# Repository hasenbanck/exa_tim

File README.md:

# EXA_tim

EXA_tim is a wristwatch that uses GNSS for time synchronization.

# Features

- 32bit STM32L0 MCU
- GNSS time synchronization (UTC)
- 1.54 inch e-paper display
- 4 buttons
- CR2032 battery

Currently we are aiming for 2-3 months of operation with one battery.

# Case

The case is designed in Fusion 360 and can be viewed here:
https://a360.co/2LLzCpt

A current snapshot is included in the source repository.

The case is designed to be 3D printable and uses a NATO strap.

If you want to 3D print them, you need to either use Fusion 360 or
FreeCAD to export the three components as STL files.

I printed them in PLA and PETG with good results. Low warp material
hightly recommended, since dimensional accuracy is key.

I designed the parts for a printer that can handle 0.1 mm clearance.
If you need looser clearance, please change the Fusion 360 user
variable "Clearance" for your needed value.

# Firmware

The firmware uses the STM32 HAL. It can be build by either using cmake
with the ARM GCC toolchain or by using Atollic TrueStudio.

For the CMAKE build, you need to provide the ARM GCC toolchain in the
PATH of your system. You can choose any CMAKE target that you like
to use. I personaly use ninja.

```bash
cd firmware
cmake -DCMAKE_TOOLCHAIN_FILE=arm-gcc-toolchain.cmake -G Ninja .
ninja
```

You can change add a ```-DCMAKE_BUILD_TYPE=Debug``` to the CMAKE
command to produce a debug build.

# Flashing

To programm the watch we are using the 10 pin 1.27mm (0.05") Cortex Debug
header. You need a programmer that can programm an ARM using the SWD
protocol.

A ST-Link V2 (and it's clones), a JLink (mini) or a blackmagic programmer
should work fine.

We included a OpenOCD file as an example how to programm the firmware.

You can also use any available flashing software available. For example:
 - OpenOCD
 - STM32CubeProgrammer
 - STM32 ST-Link utility
 - Segger J-Link JFlash (lite)

# License

The hardware components (case and PCB) are licensed under the CERN Open
Hardware Licence v1.2

The software components (firmware) are licensed under GPLv3.

The pcb/packages3d files are excluded from these license.

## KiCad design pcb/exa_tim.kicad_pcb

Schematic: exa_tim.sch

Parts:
BT1: 3034TR; BatteryHolder_Keystone_3034_1x20mm
C1, C6, C12, C13: 4.7uF; C_0603_1608Metric
C2, C3: 4pF; C_0603_1608Metric
C4, C5, C7, C9, C10, C11, C14, C17: 100nF; C_0603_1608Metric
C8, C15, C16, C18, C19, C20, C21, C22, C23, C24: 1uF; C_0603_1608Metric
D1, D2, D3, D4, D5, D6, D7: MBR0530; D_SOD-123
J1: 20021112-00010T4LF; PinHeader_2x05_P1.27mm_Horizontal
J2: FH12-24S-0.5SH(55); Hirose_FH12-24S-0.5SH_1x24-1MP_P0.50mm_Horizontal
L1: LPS4018-683MRB; L_Coilcraft_LPS4018
LS1: CUI_CSS-0575A-SMT
Q1, Q2: SI2333DS-T1-E3; SOT-23
Q3: DMN3067LW-7; SOT-323_SC-70
R1, R2, R5, R6: 1M; R_0603_1608Metric
R3, R4: 220; R_0603_1608Metric
R7: 3; R_0603_1608Metric
SW1, SW2, SW3, SW4: TL3305CF260QG; TL3305
U1: STM32L071KZUx; QFN-32-1EP_5x5mm_P0.5mm_EP3.45x3.45mm
U2: CAM-M8C-0; LCC100P960X1400X210-31N
Y1: ST2012SB32768B0HPWBB; Crystal_SMD_TXC_9HT11-2Pin_2.0x1.2mm_HandSoldering

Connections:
3V: BT1.1, C1.2, C4.2, C6.2, C7.2, C8.2, C9.2, C10.2, C13.1, J1.1, L1.1, Q1.2, Q2.2, R2.2, R5.2, SW1.1, SW2.1, SW3.1, SW4.1, U1.5 (VDDA), U1.17 (VDD), U1.24 (VDDIO2), U1.32 (VDD)
/ALARM: LS1.1, U1.7 (PA1)
/BTN1: D1.2, SW1.2, U1.27 (PB5)
/BTN2: D2.2, SW2.2, U1.26 (PB4)
/BTN3: D3.2, SW3.2, U1.29 (PB7)
/BTN4: D4.2, SW4.2, U1.28 (PB6)
/BUSY: J2.9, U1.12 (PA6)
/CS: J2.12, U1.18 (PA8)
/DC: J2.11, U1.14 (PB0)
/DISP_EN: Q2.1, R5.1, U1.10 (PA4)
/GDR: J2.2, Q3.1, R6.1
/GNSS_EN: Q1.1, R2.1, U1.22 (PA12)
/MOSI: J2.14, U1.13 (PA7)
/NRST: C5.2, J1.10, U1.3 (NRST)
/PREVGH: C21.1, D7.1, J2.21
/PREVGL: C23.1, D6.2, J2.23
/RESE: J2.3, Q3.2, R7.1
/RESET: J2.10, U1.15 (PB1)
/RF: U2.16, U2.17
/RX: R3.2, U1.9 (PA3)
/RX_GNSS: R4.1, U2.26
/SCK: J2.13, U1.11 (PA5)
/SWCLK: J1.4, U1.25 (PA14)
/SWDIO: J1.2, U1.23 (PA13)
/TX: R4.2, U1.8 (PA2)
/TX_GNSS: R3.1, U2.25
/VDD_DISP: C17.1, J2.15, J2.16, Q2.3
/VDD_GNSS: C12.2, Q1.3, U2.1, U2.8, U2.9
/WKUP1: C11.1, D1.1, D2.1, D3.1, D4.1, U1.6 (PA0)
unnamed: C2.1, U1.1 (PC14), Y1.1
unnamed: C3.1, U1.2 (PC15), Y1.2
unnamed: C14.1, D5.2, D6.1
unnamed: C14.2, D7.2, L1.2, Q3.3
unnamed: C15.1, J2.4
unnamed: C16.2, J2.5
unnamed: C18.1, J2.18
unnamed: C19.1, J2.19
unnamed: C20.1, J2.20
unnamed: C22.1, J2.22
unnamed: C24.1, J2.24
unnamed: R1.2, U1.30 (BOOT0)

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
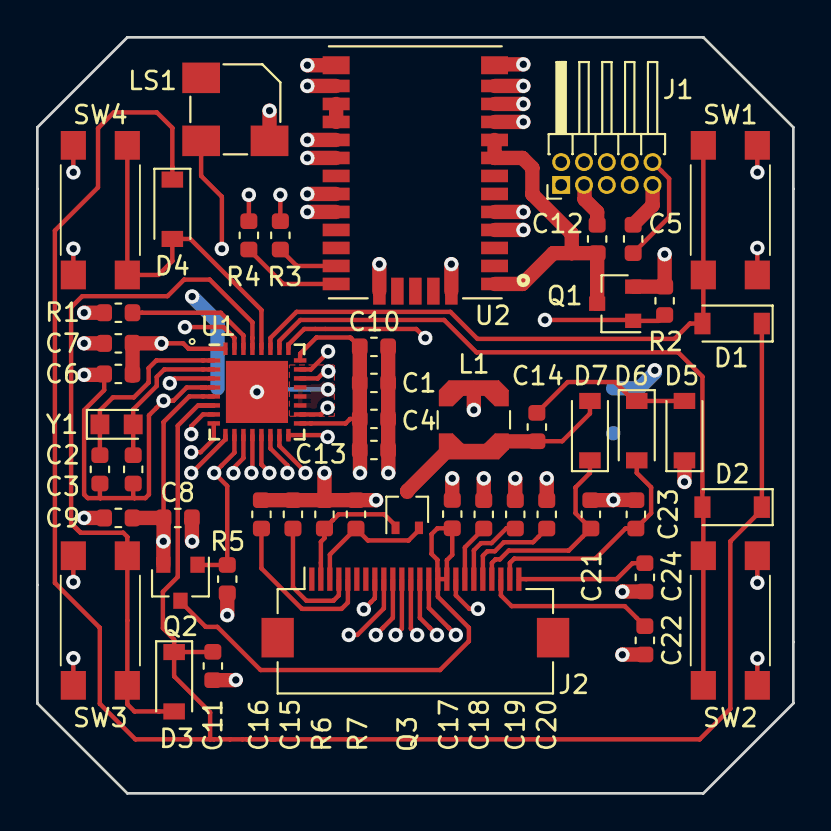
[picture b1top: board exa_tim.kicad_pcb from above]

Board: 4 copper layers, 42.0 x 42.0 mm, 53 parts (1 on the bottom side), 42 nets.

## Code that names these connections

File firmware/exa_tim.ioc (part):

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Mcu.Name=STM32L071K(B-Z)Ux
Mcu.Package=UFQFPN32
Mcu.UserName=STM32L071KZUx
PA0.Mode=SYS_WakeUp0
PA0.Signal=SYS_WKUP1
PA1.GPIOParameters=GPIO_Speed,GPIO_Label
PA1.GPIO_Label=ALARM
PA1.GPIO_Speed=GPIO_SPEED_FREQ_HIGH
PA1.Signal=S_TIM2_CH2
PA10.Signal=GPIO_Analog
PA11.Signal=GPIO_Analog
PA12.GPIOParameters=GPIO_Label
PA12.GPIO_Label=GNSS_EN
PA12.Signal=GPIO_Output
PA13.Mode=Serial_Wire
PA13.Signal=SYS_SWDIO
PA14.Mode=Serial_Wire
PA14.Signal=SYS_SWCLK
PA2.Mode=Asynchronous
PA2.Signal=LPUART1_TX
PA3.Mode=Asynchronous
PA3.Signal=LPUART1_RX
PA4.GPIOParameters=GPIO_Label
PA4.GPIO_Label=DISP_EN
PA4.Signal=GPIO_Output
PA5.Mode=TX_Only_Simplex_Unidirect_Master
PA5.Signal=SPI1_SCK
PA6.GPIOParameters=GPIO_Label
PA6.GPIO_Label=BUSY
PA6.Signal=GPIO_Input
PA7.Mode=TX_Only_Simplex_Unidirect_Master
PA7.Signal=SPI1_MOSI
PA8.GPIOParameters=GPIO_Label
PA8.GPIO_Label=CS
PA8.Signal=GPIO_Output
PA9.Signal=GPIO_Analog
PB0.GPIOParameters=GPIO_Label
PB0.GPIO_Label=DC
PB0.Signal=GPIO_Output
PB1.GPIOParameters=GPIO_Label
PB1.GPIO_Label=RESET
PB1.Signal=GPIO_Output
PB4.GPIOParameters=GPIO_Label
PB4.GPIO_Label=BTN2
PB4.Signal=GPIO_Output
PB5.GPIOParameters=GPIO_Label
PB5.GPIO_Label=BTN1
PB5.Signal=GPIO_Output
PB6.GPIOParameters=GPIO_Label
PB6.GPIO_Label=BTN4
PB6.Signal=GPIO_Output
PB7.GPIOParameters=GPIO_Label
PB7.GPIO_Label=BTN3
PB7.Signal=GPIO_Output
PC14-OSC32_IN.Mode=LSE-External-Oscillator
PC14-OSC32_IN.Signal=RCC_OSC32_IN
PC15-OSC32_OUT.Mode=LSE-External-Oscillator
PC15-OSC32_OUT.Signal=RCC_OSC32_OUT
RCC.SYSCLKFreq_VALUE=16000000
RCC.SYSCLKSource=RCC_SYSCLKSOURCE_HSI
board=custom

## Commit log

2018-08-20 Initial commit of exa_tim
    A PCB for a watch that has following features:
    - 32bit STM32L0 MCU
    - GNSS for getting the current UTC time
    - e-paper as a display
    PCB size is 42x42mm
2018-08-20 Add .gitignore file
2018-08-20 Add name, version and fab instructions to PCB
2018-08-20 General cleanup
2018-08-23 Rework GND plane, power distrubution and PU
    PU are now 1M ohm. GND is the only power plane.
2018-08-25 Added 3d models and moved some parts for fitting
    The 3d models are not licenced under the permissive licensce.
    They come from their manufacturer and some other free sources.
2018-08-25 Fix hirose connector 3d model placing
2018-08-25 Changed epaper connection to bottom feeding
    Switched from FH12A to FH12, which is bottom feeding. This way the
    PCB doesn't need to be mounted with the top facing down.
    Also moved the battery now back to the original version. Hopefully
    the battery will fit properly.
2018-08-25 Rework PCP for more compact size
    I reworked the PCB layout to archive a more compact
    PCB layout / size. This should make the construction of
    the watch casing much more easier.
    Maybe we need to change the switches for a more fitting
    design (maybe SMD mounted switches).
2018-08-27 Change battery to CR2032 for better height profile
2018-08-27 Use different buttons to get thinner design
    I used other buttons and relocated the buttons and the
    SWD connector to the bottom of the PCB to get a much
    thinner design. PCB will use a 1mm board.
2018-08-28 Cut PCB for buttons
2018-08-30 Revert PCB cutout and change button layout
    Buttons are not top facing for easier assembly.
    First inner layer is now power lane.
    Removed useless LED, since we have no way to illuminate
    the epaper display.
2018-08-30 Chang Cortex Debug header to right angle TH
2018-08-31 Rework the project structure
    This way we can integrated firmware and case CAD files.
2018-08-31 Add image to README.txt
2018-08-31 Rework ground and power plane
2018-08-31 Add snapshot of case
    Designed in Fusion 360, exported as IGES files (can be opened
    in FreeCad).
2018-08-31 Add message that only precious few will understand
2018-08-31 Rework power plane and GND of STM32L0 chip
2018-08-31 Change crystal caps from 21 to 20pF
2018-09-01 Add BOM for the PCB components
2018-09-01 Updated README.md and CASE CAD iges file
2018-09-03 Add firmeware template and renamed PCB folder to pcb
    You can build the firmware by either using make or Atollic True
    Studio.
2018-09-03 Optimize build
2018-09-03 Add tiny_printf.c for smaller printf instructions
2018-09-03 Clean up Makefile
2018-09-03 Add first iteration of OpenOCD file
    This file hasn't been tested yet, since I don't have a working
    prototype for programming yet.
    I persoanly use a JTAG edu-mini, but any OpenOCD compatible
    SWD programmer should work.
2018-09-03 Add information about flashing to README.md
2018-09-03 Remove syscalls.c
    We don't need it in this project, since we can't add debugg log
    using SWO (Not supported by M0).
2018-09-08 Remove LED pin from STM32 Cube configuration file
2018-09-08 Add u8g8 library and used clang-format
    clang-format in the default formatting style is the future
    coding style to use. Using simple default values to don't
    get involved in any coding style discussion.
2018-09-08 Fix compilation error
2018-09-08 Fix Atollic Studio compilation
2018-09-08 Fixed LICENSE.txt
    Handled special case of middleware folder.
2018-09-09 Add SEGGER RTT for fast debug logging
    Since we don't have SWO debugging available on a M0+ core,
    we need a way to get debug logs.
    Semihosting is incredible slow, so we use the RTT implementation
    of SEGGER. The software part is open source. The only hardware
    that implements RTT are the J-Link programmer by SEGGER themself.
2018-09-09 Reduce the RAM usage of the RTT library
    We only have 20k or RAM, so I reduced the RAM usage of the RTT
    library.
2018-09-09 Add simpler logging macro and extend Error_Handler
2018-09-09 Add initial display handling
2018-09-10 Add LPTIM1 to configuration
2018-09-10 Add LPTIM1 for later usage for button debouncing
    Firing interrupts at 5ms. Should be stopped once watch
    goes into sleep mode.
2018-09-10 Add first try of a button debounce algorithm
    Also changed the interrupt priority of some interrupts.
2018-09-10 Fix the debounce algorithm
    C has the shift operation the other way around.
    I also added a little desciption to the algorithm.
2018-09-11 Add new debouncer code and activated LTO
2018-09-11 Simplified the Makefile
2018-09-11 Fix clang-format formatting
    VS Code falled back to the Visual Studio style.
    We now include a .clang-format with a LLVM style.
2018-09-11 Add a CMAKE file for MAKE and NINJA support
2018-09-11 Fix CMake builds and added a "ninja" example
    I'm still not sure why the cmake and make build is different in size.
2018-09-11 Remove old makefile
    You can now use CMAKE to create a makefile or a ninja build script.
2018-09-11 Add default build target and changed .gitignore
2018-09-11 Add a tasks.json file for Visual Studio Code
2018-09-12 Fix VS Code integration
2018-09-12 Remove unused CLANG toolchain, optimized CMakeLists
    The CLANG toolchain isn't usefull as of right now, since I
    can't find a way to get it working. I can't find a way to
    configure the linker to produce something usefull.
2018-09-12 Add device definition for debugging in VS code
2018-09-12 Change debugger name to a better name
2018-09-14 Changed 2x06 header to 2x05 header
    I choosed the wrong header for the Cortex Debug header.
    This is the correct header. The old header is working fine
    but two holes are not used.
2018-09-14 Simple loop to start programming
2018-09-15 Fix various small bugs and added test draw
2018-09-15 Fix p-channel MOSFET and new routing
    Fixed the p-channel MOSFET drain/source problem (was reversed).
    New placement for the SWO header (2x05) for easier placement.
    Re-routed signals, so that ground and power lane are signal trace
    free.
2018-09-15 Reroute some GND vias
2018-09-15 VS Code shoudl build project before debug
2018-09-15 Move epaper display connector more upward
    This is needed, since the flexible connector hangs out too
    much and wouldn't fit into the case otherwise.
2018-09-15 Add self made keihansoukaishi number fonts
    Numbers as used in EXA_pico universe primarly on ra_Ciela.
2018-09-16 Add new font, add alarm, removed alarm series resistor
    The series resistor was not needed, since the alarm would be too
    tiny. I also added basic "beep" functionality.
    Also added a new font face size 96.
2018-09-16 Fixed button presse detection
2018-09-16 Removed SPI DMA and optimized display handling
2018-09-16 Changed powerdown sequence of the display
    We will need to handle the display like we would handle it on
    power up. So just initalize it.
2018-09-16 Chang GNSS MOSFET to enh. N-Channel
    Changed the MOSFET so that we don't need a pullup,
    which might draw some precious power we don't want to
    waste.
    Also simplifies the BOM.
2018-09-17 First pass to re-arange parts to move connector
2018-09-17 Switched backt to high side p-channel MOSFET
    I don't want to risk communication errros of UART
    because of the otherwise not common ground levels.
2018-09-17 Second pass to reloacte many components up for connector placement
2018-09-18 Redesigned LSE layout and re-routed some traces
    Also switched BTN3 and BTN4 pins for easier routing.
2018-09-18 Add SVD file and lowered LSE drive current
    I already use a 6pf crystall and still can't get it to run
    under RCC_LSEDRIVE_LOW or RCC_LSEDRIVE_MEDIUMLOW.
2018-09-18 Need to raise LSE drive strength because of instability
2018-09-18 First try to implement a pwr logic
2018-09-19 Snapshot
2018-09-19 Fixed display power down and button wakup
    TODO: RTC wakeup recognition (wakeup is not called)
2018-09-19 Reworked wakup logic and time rendering
    When debugging the RTC gives odd values and I can't differentiate
    between normal standby wakeup and debug start.
2018-09-19 Fix RTC accuracy and running the watch under debug
    But running the watch without debug is now broken ...
    I can't seem to find a good way to distinguish between
    PWR ON and resuming from STANDBY.
2018-09-19 Optimized the display update routine
2018-09-19 Fixed RTC timekeeping
2018-09-20 Fix build using cmake/ninja
2018-09-20 Optimize display refresh
2018-09-20 Switched LSE crystall for achieving LOW drive capability
    It seems my oscilloscope is interfering wit LSE
    operation when measuring and having the LOW drive
    capability on.
    But the LSE seeem to work fine, since the RTC and LPTIM
    seem to work fine under it.
2018-09-20 Add third MOSFET to shutdown E-Paper driver
    This will cut off the e-paper from any voltage source
    and should result in an even lower power usage.
2018-09-22 First try to display a simple menu
2018-09-22 Fix some compilation errors under clang.
2018-09-22 Implement basic application logic
    Better abstraction for later function extension.
2018-09-22 Update pictures of the PCB
2018-09-23 Added low power warning
    Using the internal PVD. Set around 2.7V.
2018-09-24 Rework build process, debugging logging and PVD
2018-09-24 Removed RTT
    RTT doesn't work well in the current configuration.
    Maybe it's a memory leak in U8G2?
2018-09-24 Optimize SSD1607 routines for speed
    I primarely removed some delays and the init sequence for
    the first init.
    Since we shutdown the whole module and update the screen every
    minute as the "first init", the refresh takes rather long.
    This removed the first "white / black" clearing.
    Long term effect unknown.
2018-09-24 Optimized display refresh
    Once every hour the display will do a proper init of the display
    pixels. I hope that this will improve the lifetime of the
    display pixels.
2018-09-24 Code cleanup and trying to find 01:00 bug
    "01:00" bug stops the whole MCU after printing "01:00" to the
    watchface.
    But this only happens when starting at 00:59. Starting at 01:00
    works fine. 01:59 also works fine.
2018-09-25 Fix "01:00" bug
    The TimerB was set to 01:00, which resulted in halting the MCU
    when going into standby when the TimerB was active.
    I reworked the timer logic and now the MCU doesn't freeze anymore.
    We don't need an interrupt, since our timer are only minute sensitive
    and we wake up the MCU every minute anyhow.
2018-09-25 Fix PVD bug
    We need to move the check to a later call time, since the
    PVD might not be ready.
2018-09-25 Add configuration items and styled the conf menu
2018-09-25 Finish the configuration menu
2018-09-25 Add two time.h conversion functions
    For later UTC to CHIP time
2018-09-26 Add timezone library
    RTC clock runs in UTC. Time display is localtime.
    If the alarm is updated, it also need to be converted from
    localtime to UTC and saved as such inside the RTC.
    GNSS sync time also needs to be saved as such when updating
    the timezone.
2018-09-26 Update timezone configuration
    Alarms are not working as intended yet.
2018-09-26 Removed debug menue entry
2018-09-27 Reworked timer logic
    It's not RTC based anymore, which is fine.
    Somehow the button debounce needed a shorter timer interrupt.
2018-09-27 Some small formatting
2018-09-29 Implement timer based alarm
    The watch now uses sleep mode when running the timer for the alarm.
2018-09-30 Add date, more symbols and version on display
2018-10-01 Change enable pins for new board design
